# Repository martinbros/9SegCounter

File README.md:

# Nine Segment Counter SAO

**Description**

Use this handy little SAO to count whatever your heart desires: how many conversations you have at Supercon, how many times someone asks what SAO stands for, how many times someone asks "What are you working on?".
By using the onboard buttons, I2C interface, or clocking the GP2 pin, the Nine Segment Counter SAO will indicate to the world whatever quantity you are keeping track of.

## Operation

Store a 2 digit number and display the number using an atypical 9 segment display instead of the typical 7

Using the buttons, a user can store 49 unique numbers in non-volatile memory. Each unique number is identified by the color of the digits.

Using the I2C bus, the user has full read and write access to the ATTiny 84's 512 byte EEPROM and has full command of the display (displayed number and digit color).

### Button Interface

- Pressing a button above a digit increases that digit by 1
- Pressing a button below a digit decreases that digit by 1
- The displayed digit is stored as a decimal 2 digit number (0-99)
- Pressing the buttons above and below a digit simultaneously changes the color of that digit
  - Each unique two digit color combination corresponds to a unique number saved in non-volatile memory
  - 7 unique colors per "ones" digit x 7 unique colors per "tens" digit = 49 unique values stored in non-volatile memory
  - EEPROM Address location is built by taking the "ones" position color index (0-6) and adding it to the "tens" position color index which has been multipled by 10 (0-6 x 10) [e.g. 00, 02, 03 ... 07, 10, 11 ... 17, 20 ... 27 ... 77]

### I2C Interface

- I2C Address: 4

**Display Functions**

- 1 8-bit message: the display will update to show the sent number (Displayed number is not stored in memory)
- 3 8-bit messages: set the RGB values of the digits to be displayed (Digit must be refreshed to update color)
- 6 8-bit messages: set the RGB values of the tens place digit and then ones place digit (Digit must be refreshed to update color)

**Memory Functions**

- 2 8-bit message: The sent number is converted to a 16-bit EEPROM address pointer, the display will update to display the value stored in memory.
- 4 8-bit messages: first 2 bytes are combined to a 16-bit EEPROM address pointer, third byte is the data to be stored in the EEPROM, the last byte is a throwaway
- 5 8-bit messages: The entire EEPROM is filled with the contents of the first message, the remaining 4 messages are discarded

### GP1 Interface

- GP1 is normally pulled high. By driving GP1 low, the displayed number will be incremented by 1
- Max clock speed is ~150Hz
- Displayed number is not stored in memory 

### GP2 Interface

- GP2 is connected directly to the first Neopixel and is terminated with a 470 ohm resistor. If you desire, feel free to implement the Neopixel protocol and set the segments however you like! Use the reference photo below for the sequence of the neopixels.

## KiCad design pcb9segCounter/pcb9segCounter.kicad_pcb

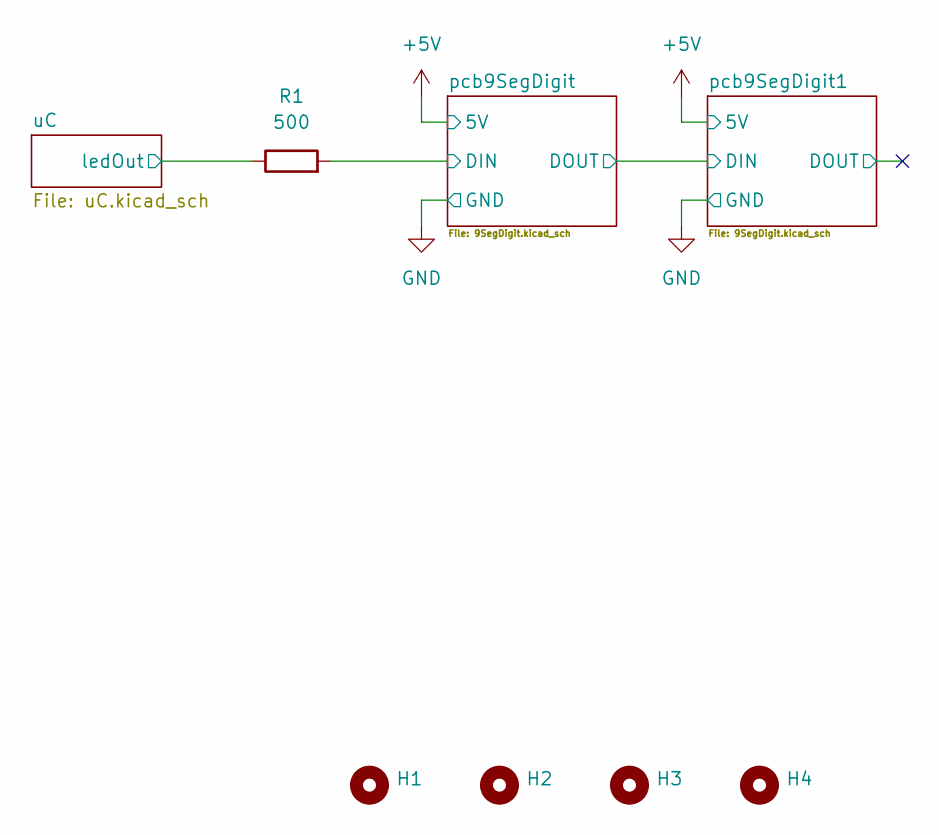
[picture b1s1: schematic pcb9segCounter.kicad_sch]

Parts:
H1, H2, H3, H4: MountingHole_2.2mm_M2_ISO7380
R1: 500; R_0805_2012Metric

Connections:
/pcb9SegDigit/DIN: R1.2; also elsewhere on the board
GP2: R1.1; also elsewhere on the board

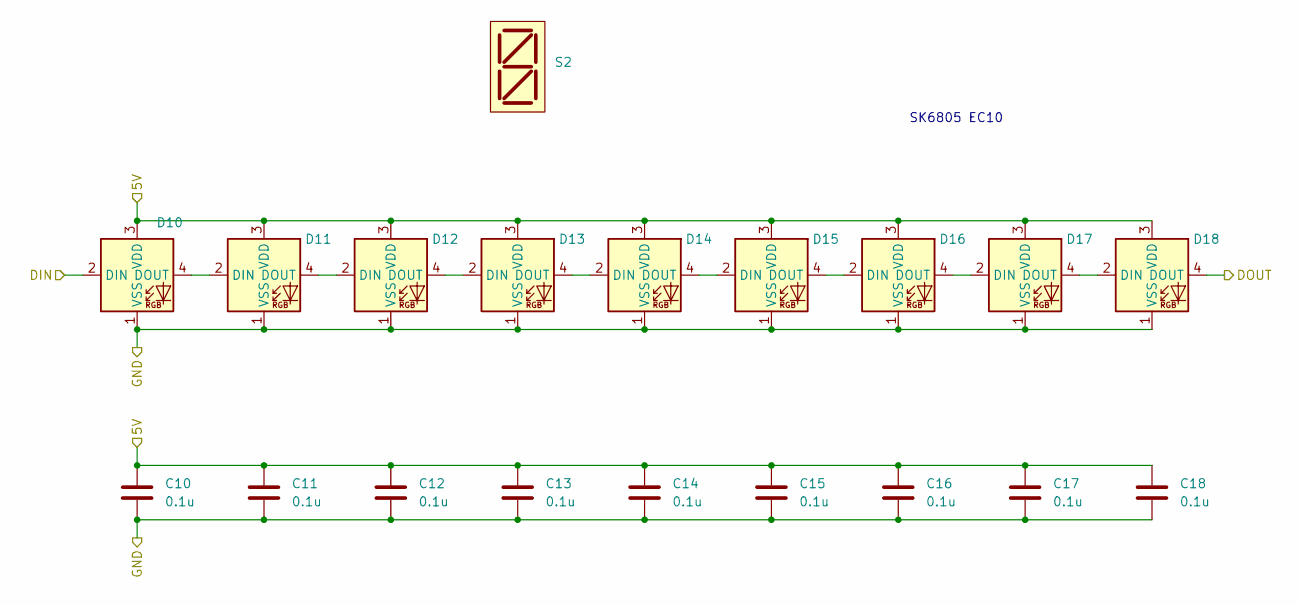
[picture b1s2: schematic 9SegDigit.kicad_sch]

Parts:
C10, C11, C12, C13, C14, C15, C16, C17, C18: 0.1u; C_0805_2012Metric
D10, D11, D12, D13, D14, D15, D16, D17, D18: 1x1mm SMD RGB LED; MPN SK6805-EC10
S2: 9 Segment 38x19x3

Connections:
+5V: C10.1, C11.1, C12.1, C13.1, C14.1, C15.1, C16.1, C17.1, C18.1, D10.3 (VDD), D11.3 (VDD), D12.3 (VDD), D13.3 (VDD), D14.3 (VDD), D15.3 (VDD), D16.3 (VDD), D17.3 (VDD), D18.3 (VDD); also elsewhere on the board
/pcb9SegDigit1/DOUT: D18.4 (DOUT)
/pcb9SegDigit/DOUT: D10.2 (DIN); also elsewhere on the board
GND: C10.2, C11.2, C12.2, C13.2, C14.2, C15.2, C16.2, C17.2, C18.2, D10.1 (VSS), D11.1 (VSS), D12.1 (VSS), D13.1 (VSS), D14.1 (VSS), D15.1 (VSS), D16.1 (VSS), D17.1 (VSS), D18.1 (VSS); also elsewhere on the board
unnamed: D10.4 (DOUT), D11.2 (DIN)
unnamed: D11.4 (DOUT), D12.2 (DIN)
unnamed: D12.4 (DOUT), D13.2 (DIN)
unnamed: D13.4 (DOUT), D14.2 (DIN)
unnamed: D14.4 (DOUT), D15.2 (DIN)
unnamed: D15.4 (DOUT), D16.2 (DIN)
unnamed: D16.4 (DOUT), D17.2 (DIN)
unnamed: D17.4 (DOUT), D18.2 (DIN)

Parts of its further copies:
C1, C2, C3, C4, C5, C6, C7, C8, C9: 0.1u; C_0805_2012Metric
D1, D2, D3, D4, D5, D6, D7, D8, D9: 1x1mm SMD RGB LED; MPN SK6805-EC10
S1: 9 Segment 38x19x3

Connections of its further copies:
+5V: C1.1, C2.1, C3.1, C4.1, C5.1, C6.1, C7.1, C8.1, C9.1, D1.3 (VDD), D2.3 (VDD), D3.3 (VDD), D4.3 (VDD), D5.3 (VDD), D6.3 (VDD), D7.3 (VDD), D8.3 (VDD), D9.3 (VDD); also elsewhere on the board
/pcb9SegDigit/DIN: D1.2 (DIN); also elsewhere on the board
/pcb9SegDigit/DOUT: D9.4 (DOUT); also elsewhere on the board
GND: C1.2, C2.2, C3.2, C4.2, C5.2, C6.2, C7.2, C8.2, C9.2, D1.1 (VSS), D2.1 (VSS), D3.1 (VSS), D4.1 (VSS), D5.1 (VSS), D6.1 (VSS), D7.1 (VSS), D8.1 (VSS), D9.1 (VSS); also elsewhere on the board
unnamed: D1.4 (DOUT), D2.2 (DIN)
unnamed: D2.4 (DOUT), D3.2 (DIN)
unnamed: D3.4 (DOUT), D4.2 (DIN)
unnamed: D4.4 (DOUT), D5.2 (DIN)
unnamed: D5.4 (DOUT), D6.2 (DIN)
unnamed: D6.4 (DOUT), D7.2 (DIN)
unnamed: D7.4 (DOUT), D8.2 (DIN)
unnamed: D8.4 (DOUT), D9.2 (DIN)

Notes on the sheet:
SK6805 EC10

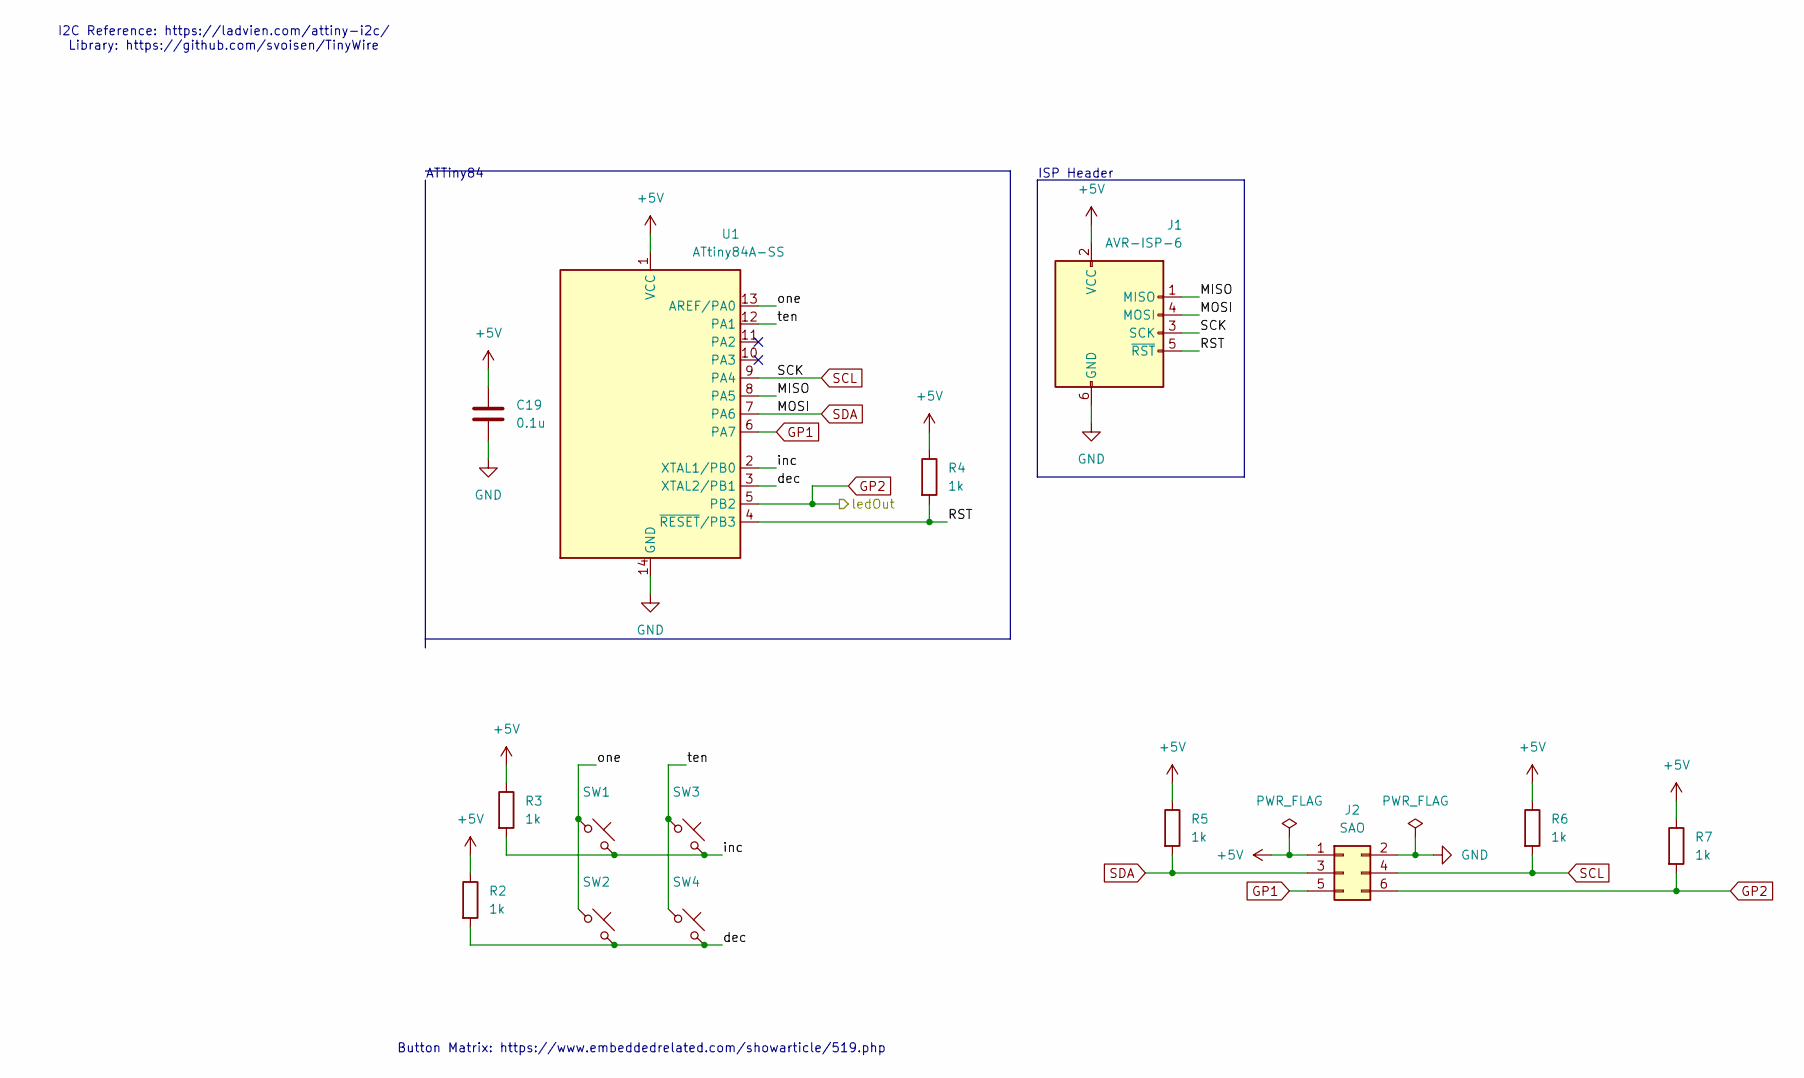
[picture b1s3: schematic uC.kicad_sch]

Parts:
C19: 0.1u; C_0805_2012Metric; mouserPN 80-C0805C104M3R
J1: AVR-ISP-6; PinHeader_2x03_P2.54mm_Vertical; MPN 10129381-906002BLF
J2: SAO; PinHeader_2x03_P2.54mm_Vertical; MPN 10129381-906002BLF
R2, R3, R5, R6, R7: 1k; R_0805_2012Metric
R4: 1k; R_0805_2012Metric_Pad1.20x1.40mm_HandSolder; mouserPN 71-CRCW08051K00JNEAC
SW1, SW2, SW3, SW4: PTS636 SK43 LFS; MPN PTS636 SK43 LFS
U1: ATtiny84A-SS; SOIC-14_3.9x8.7mm_P1.27mm; mouserPN 556-ATTINY84-20SSU

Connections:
+5V: C19.1, J1.2 (VCC), J2.1, R2.1, R3.1, R4.1, R5.1, R6.1, R7.1, U1.1 (VCC); also elsewhere on the board
/uC/MISO: J1.1 (MISO), U1.8 (PA5)
/uC/RST: J1.5 (~RST), R4.2, U1.4 (~RESET/PB3)
/uC/dec: R2.2, SW2.2, SW4.2, U1.3 (XTAL2/PB1)
/uC/inc: R3.2, SW1.2, SW3.2, U1.2 (XTAL1/PB0)
/uC/one: SW1.1, SW2.1, U1.13 (AREF/PA0)
/uC/ten: SW3.1, SW4.1, U1.12 (PA1)
GND: C19.2, J1.6 (GND), J2.2, U1.14 (GND); also elsewhere on the board
GP1: J2.5, U1.6 (PA7)
GP2: J2.6, R7.2, U1.5 (PB2); also elsewhere on the board
SCL: J1.3 (SCK), J2.4, R6.2, U1.9 (PA4)
SDA: J1.4 (MOSI), J2.3, R5.2, U1.7 (PA6)

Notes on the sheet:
ATTiny84
ISP Header
I2C Reference: https://ladvien.com/attiny-i2c/ Library: https://github.com/svoisen/TinyWire
Button Matrix: https://www.embeddedrelated.com/showarticle/519.php

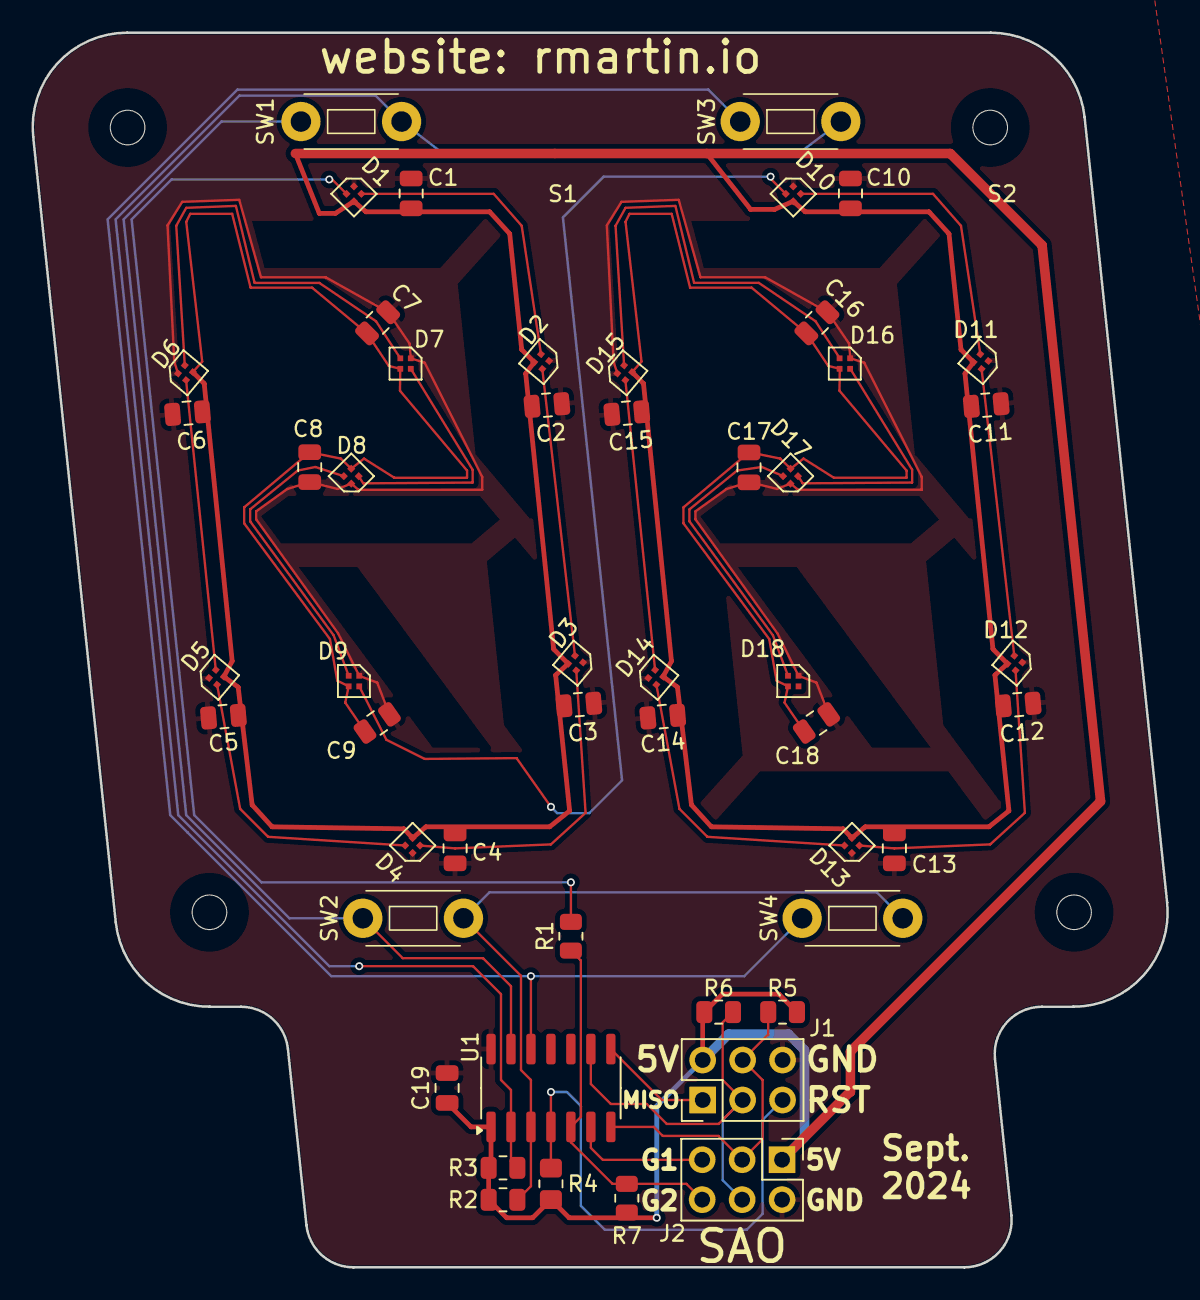
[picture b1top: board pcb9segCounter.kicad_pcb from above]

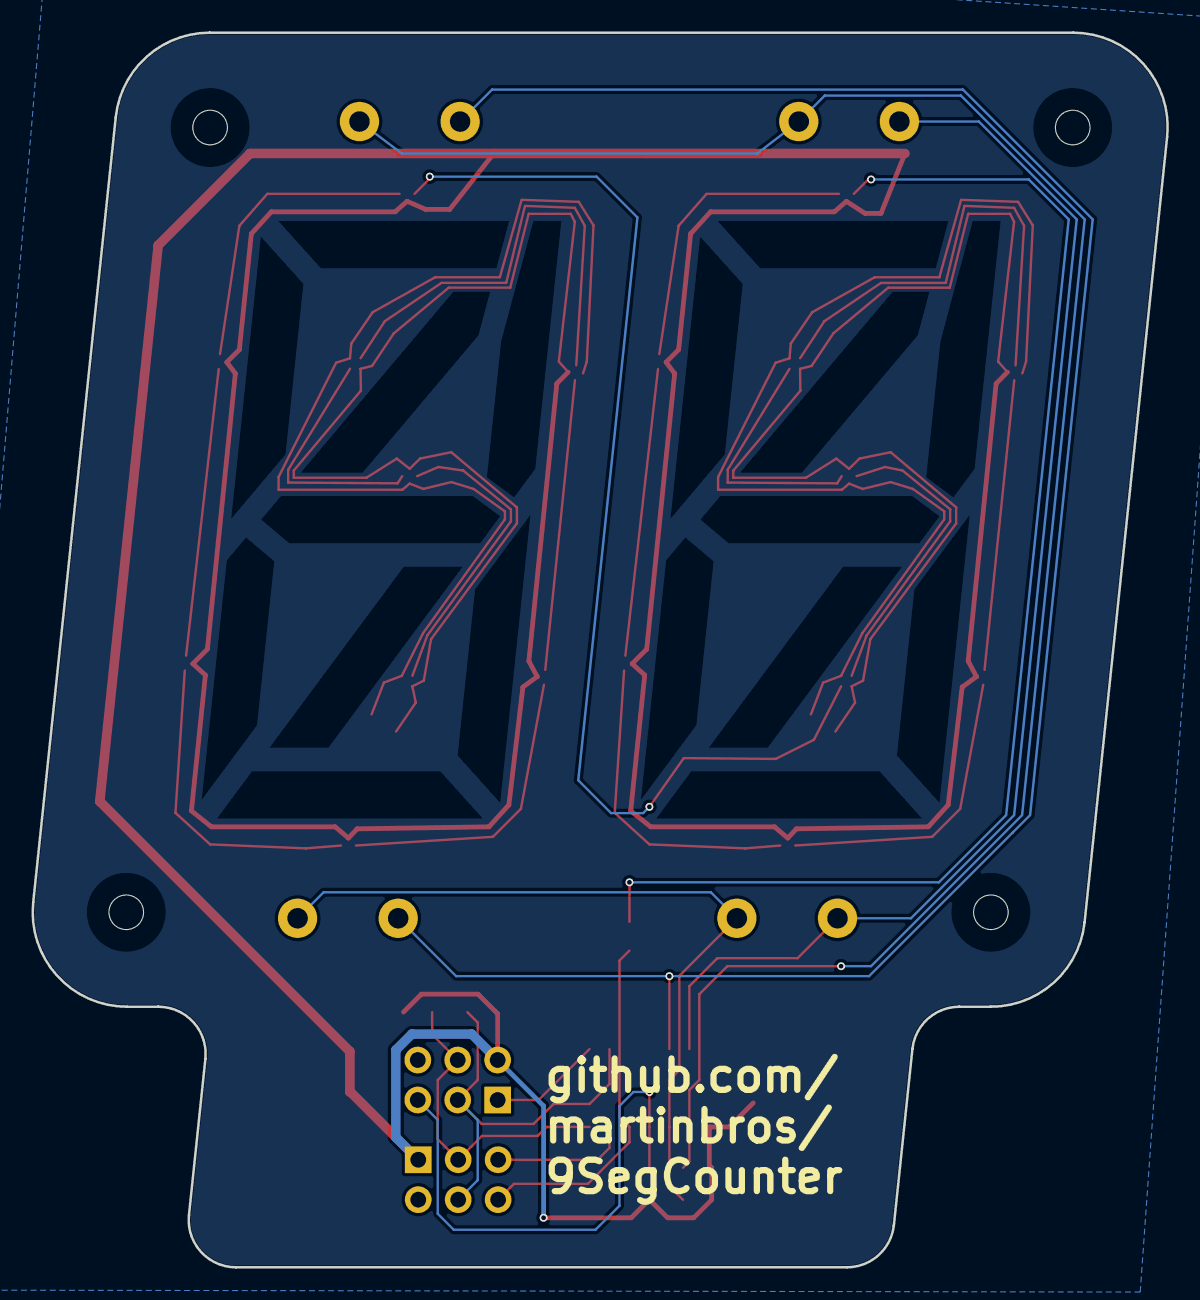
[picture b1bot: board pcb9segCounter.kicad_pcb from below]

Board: 2 copper layers, 72.2 x 78.5 mm, 57 parts (2 on the bottom side), 30 nets.

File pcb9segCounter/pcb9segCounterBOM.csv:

Reference,Value,Datasheet,Footprint,Qty,DNP,MFG,MPN
"C1,C2,C3,C4,C5,C6,C7,C8,C9,C10,C11,C12,C13,C14,C15,C16,C17,C18,C19",0.1u,~,Capacitor_SMD:C_0805_2012Metric,19,,Kemet,C0805C104K5RAC7210
"D1,D2,D3,D4,D5,D6,D7,D8,D9,D10,D11,D12,D13,D14,D15,D16,D17,D18",~,https://cdn-shop.adafruit.com/product-files/5849/SK6805-EC10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,customParts:1x1mm SMD RGB LED,18,,Dongguan,SK6805-EC10
J1,AVR-ISP-6,~,Connector_PinHeader_2.54mm:PinHeader_2x03_P2.54mm_Vertical,1,,Amphenol FCI ,10129381-906002BLF
J2,SAO,~,Connector_PinHeader_2.54mm:PinHeader_2x03_P2.54mm_Vertical,1,,Amphenol FCI ,10129381-906002BLF
R1,500,~,Resistor_SMD:R_0805_2012Metric,1,,Yago,RC0805FR-07470RL
"R2,R3,R5,R6,R7",1k,~,Resistor_SMD:R_0805_2012Metric,5,,Yago,RC0805FR-071KL
R4,1k,~,Resistor_SMD:R_0805_2012Metric_Pad1.20x1.40mm_HandSolder,1,,Yago,RC0805FR-071KL
"S1,S2",~,,customParts:9 Segment 38x19x3,2,,na,na
"SW1,SW2,SW3,SW4",~,~,customParts:PTS636 SK43 LFS,4,,C&K,PTS636 SK43 LFS
U1,ATtiny84A-SS,http://ww1.microchip.com/downloads/en/DeviceDoc/doc8183.pdf,Package_SO:SOIC-14_3.9x8.7mm_P1.27mm,1,,Microchip,ATTINY84-20SSU

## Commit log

2017-01-02 Hello world, softuart echo with attiny84
2017-01-02 Use LSB of input char to toggle an LED
2017-01-02 Write to neopixel instead of LED pin
2017-01-02 Read input as ascii hex bytes, apply to pixel buffer
2017-01-02 Print '.' and 'x' for acknowledgement
2017-01-02 Add serial controller to talk to lightbar
2017-01-02 Port and rework pixel_pi's strandtest for lightbar use
2017-01-02 Complain if no device is found
2017-01-02 README
2024-09-05 Got a good version
2024-09-07 moving files, adding more
2024-09-16 Started Routing
2024-09-18 Making progress, figuring out microcontroller interfacing
2024-09-23 Schematic looks good, going to branch to reduce the number of digits from 4 to 2
2024-09-23 Added sub-schematic and gitignore
2024-09-23 reduced to 2 digits, added capacitors
2024-09-25 Edits prior to setting board edge in freecad
2024-09-25 good routing, need to add slikscreen details
2024-09-26 adding 3d model which was used to generate board outline, commiting before adding i2c pullups
2024-09-26 Looks really good, all footprints and implementation check out. Looking to move an LED and adding an additional decap capacitor
2024-09-26 Everything looks good for manufacture
2024-09-26 Added website to board, generated gerber which was sent to oshpark for manufacture
2024-09-26 Updated details to export BOM
2024-10-03 edits to BOM and generation of HTML BOM
2024-10-05 Making edits to support SAO.
2024-10-05 Some minor cleanup post merge
2024-10-06 Edits to code and generation of the backplate segment separator
2024-10-06 Made edits to PCB file and generated gerbers for manufacture at JLCPCB
2024-10-07 Moving and renaming gerber zip files
2024-10-10 Adding README.md with documentation and potential increase in capability.
2024-10-15 Edits to Readme, found error in the schematic and made a note of it, added EEPROM capability to the code.
2024-10-16 Edits to readme, successful implementation of the "clock in" functionality on G1
2024-10-16 rebase of TinyWire repo authored by Eero af Heurlin <eero.afheurlin@iki.fi> & Sean Voisen <sean@voisen.org>
    rebase executed by "git rebase --root -i"
    Atmel app notes about USI and I2C
    reformat and add a comment about a certain weird bug
    reorg for github
    added func for returning the actual amount of data in the read buffer (and commented out the possibly-all-call-but-probably-bug)
    added orifinal source
2024-10-16 Changed makefile, was able to successfully upload working code
2024-10-16 successful compilation of i2cTest.cpp
2024-10-17 attempting to have LED debug
2024-10-17 Got some acknowledgement using buspirate, need to investigate more.
2024-10-18 figured out a lot of my issues were how to use Bus Pirate, edited makefile to allow for terminal interaction
2024-10-18 it compiles but the first byte when reading is wrong
2024-10-18 successful compile, upload, and operation of board using the updated of Makefile
2024-10-19 successful use and compilation of the libraries. Ready for use.
2024-10-19 Adding bat files
2024-10-20 code compiles and standard button use works
2024-10-20 Compiles an uploads, need to work on I2C usage
2024-10-20 able to display sent numbers after a request for data, weird
2024-10-21 progresss on I2C
2024-10-22 Corrected pointer issues as the data would not be stored in the correct location in EEPROM
2024-10-22 Sent I2C data is successfully displayed, also successful interpretation of number of bytes in message
2024-10-22 i2c number display works, one didgit color set works, two digit color set works. Weirdly starts on the second index of the colors array.
2024-10-22 Everything works well except for I2C setting data and reading back data over I2C
2024-10-22 Implemented reading and writing to EEPROM over I2C
2024-10-22 Added comments and update README, need to investigate why clock and LED seem to be on the same pin
2024-10-22 Looks like the clocking issue was due to the PCB being connected to the AVRISP MKII. Made a minor change to how data is written to memory.
2024-10-24 Seems like sending a message with a length of 5 is interpreted as a length of 6 and the color gets set. Here's the series of commands [8 100 100 0 0 100 100] --> setting color, tens place is yellow, 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
2024-10-24 Found the error, forgot a break.
2024-10-25 Doing lots of cleanup
2024-10-25 Adding Photos
2024-10-26 Good test on SN0 I am able to drive the LEDs using the BusPirate, still need to figure out why SN1 drives all LEDs to white when powering up. I am able to drive the LEDs of SN1 when the AVR pin is hi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
2024-10-26 Updated Makefile to include fuse setting parameters
2024-10-28 Added assembly instructions to schematic, generated PDFs, Updated README, Upped LED brightness
2024-10-29 Good implementation of color cycling and self clocking
2024-11-01 Updated makefile to work with 3.3v, changed model to incorporate new mounting style
2025-01-23 Adding License
2025-10-31 update fuse values to reflect change for lower brownout voltage
